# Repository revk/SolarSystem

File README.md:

# SolarSystem

Now at [Codeberg](https://codeberg.org/RevK/SolarSystem)

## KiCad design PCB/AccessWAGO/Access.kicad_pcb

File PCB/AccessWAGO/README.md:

# Access

These files are for use in [KiCad](https://www.kicad.org).

## Trademark

This is an open source project, but bear in mind you cannot sell boards bearing the Andrews & Arnold Ltd name, the A&A logo, the registered trademark AJK logo, or the GS1 allocated EANs assigned to Andrews & Arnold Ltd.

## Images

*Auto generated 2025-08-13T09:46:36*

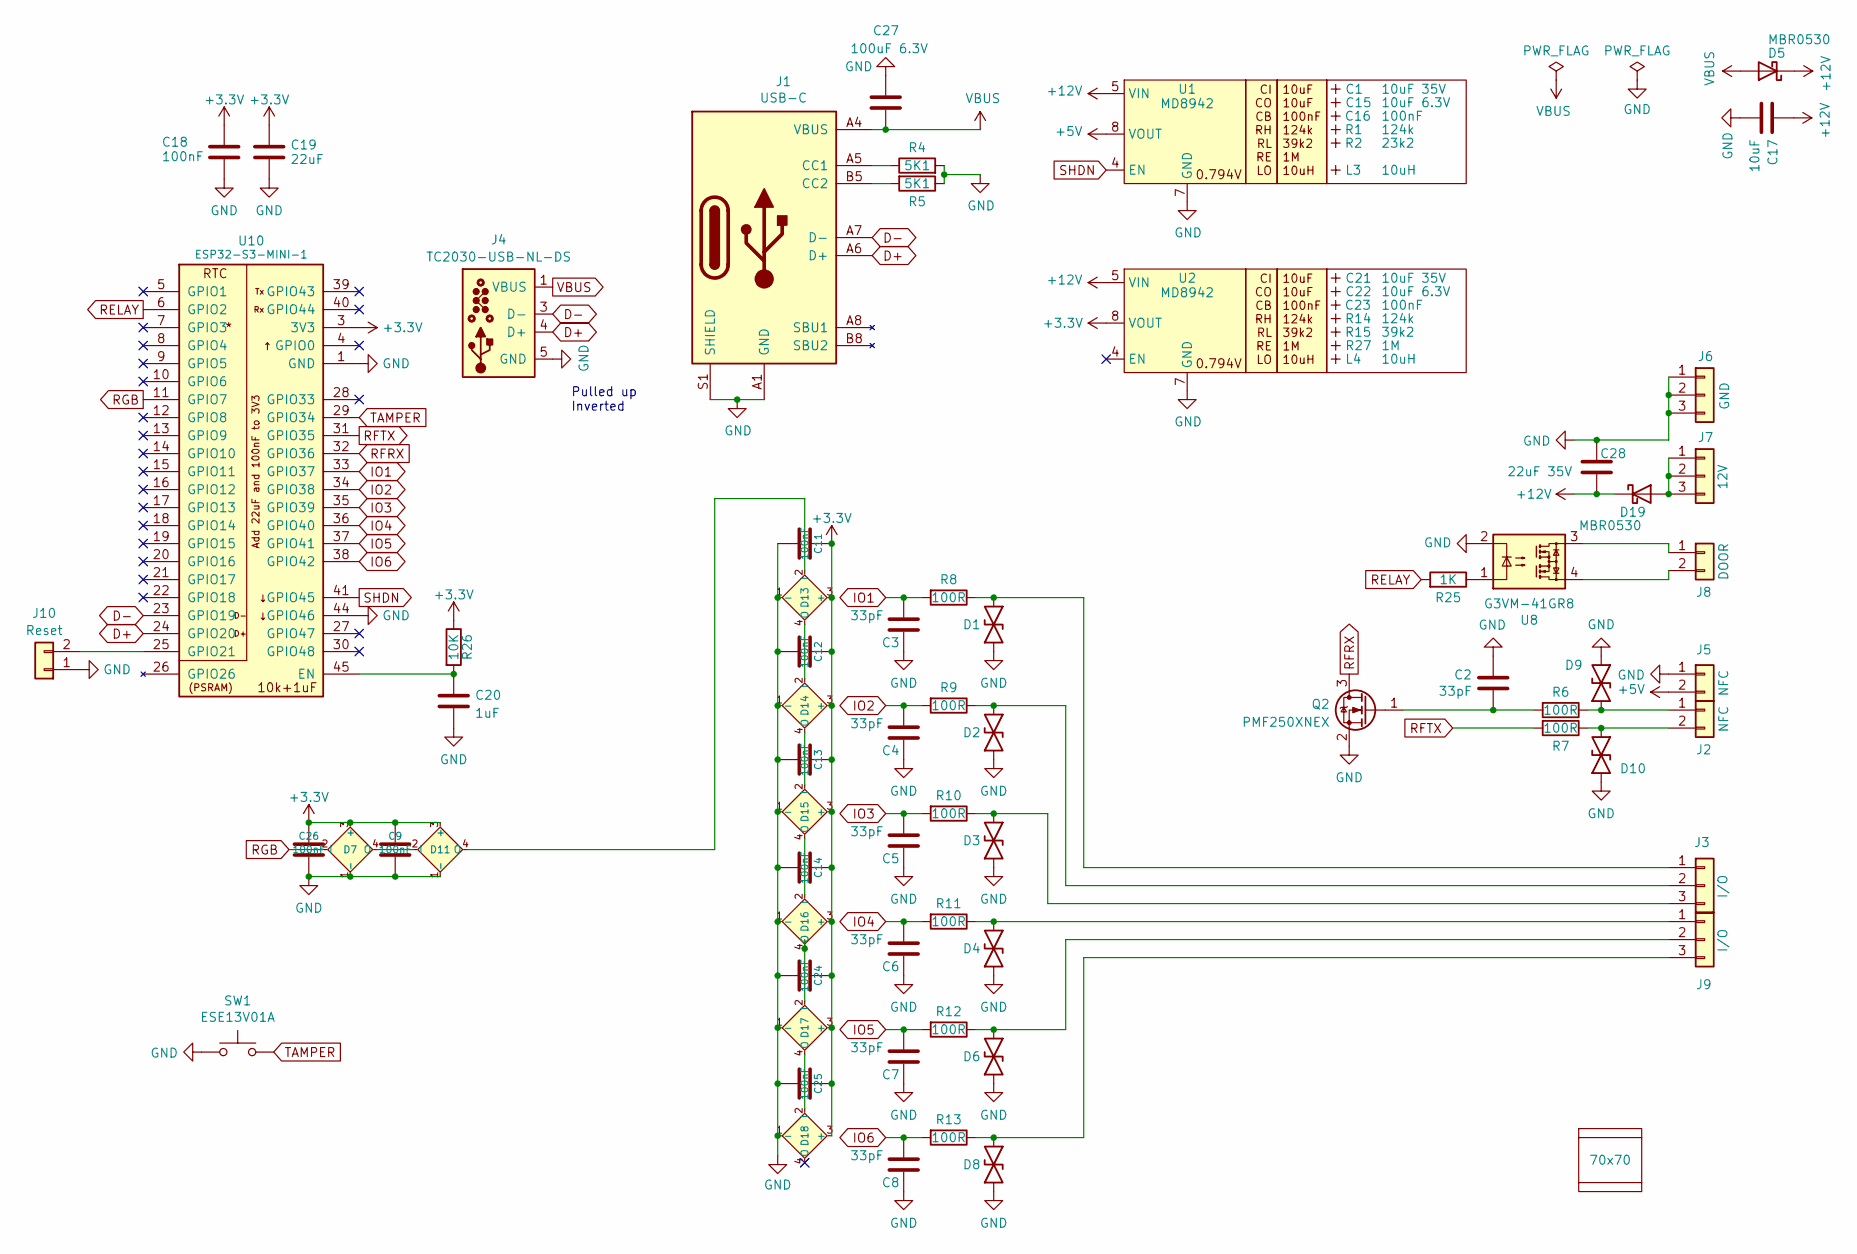
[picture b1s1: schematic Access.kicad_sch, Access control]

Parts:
C1, C21: 10uF 35V; C_0603_; MPN C194427
C2, C3, C4, C5, C6, C7, C8: 33pF; C_0201
C9, C18, C26: 100nF; C_0201
C11, C12, C13, C14, C24, C25: 100nF; C_0402
C15, C22: 10uF 6.3V; C_0603_; MPN C1691
C16, C23: 100nF; C_0603_
C17: 10uF; C_0402
C19: 22uF; C_0402
C20: 1uF; C_0201
C27: 100uF 6.3V; C_1206
C28: 22uF 35V; C_1210
D1, D2, D3, D4, D6, D8, D9, D10: DFN1006-2L; MPN C5137770
D5, D19: MBR0530; D_SOD-123; MPN C5204746
D7, D11, D13, D14, D15, D16, D17, D18: XL-1010RGBC-WS2812B; SMD1615; MPN C5349954
J1: USB-C; USB-C-Socket-H; MPN C709357
J2, J5: NFC; WAGO-2060-452-998-404-S; MPN C2765055
J3, J9: I/O; WAGO-2060-453-998-404-S; MPN C2765056
J4: TC2030-USB-NL-DS; Tag-Connect_TC2030-IDC-NL_2x03_P1.27mm_Vertical
J6: GND; WAGO-2060-453-998-404-S; MPN C2765056
J7: 12V; WAGO-2060-453-998-404-S; MPN C2765056
J8: DOOR; WAGO-2060-452-998-404-S; MPN C2765055
J10: Reset; AA-Pad
L3, L4: 10uH; L_4x4_; MPN C167879
PCB1: 70x70; PCB7070
Q2: PMF250XNEX; SOT-323_SC-70; Part No PMF250XNEX
R1, R14: 124k; R_0402_
R2: 23k2; R_0402_
R4, R5: 5K1; R_0201
R6, R7, R8, R9, R10, R11, R12, R13: 100R; R_0201
R15: 39k2; R_0402_
R25: 1K; R_0201
R26: 10K; R_0201
R27: 1M; R_0402_
SW1: ESE13V01A; ESE13
U1, U2: MD8942; SOT-23-6-MD8942; MPN C2684786
U8: G3VM-41GR8; SO-4_4.4x4.3mm_P2.54mm; MPN C2691601
U10: ESP32-S3-MINI-1; MPN C3013941
V1, V2: VCUT70

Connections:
+3.3V: C9.1, C11.1, C12.1, C13.1, C14.1, C18.1, C19.1, C24.1, C25.1, C26.1, D7.3 (+), D11.3 (+), D13.3 (+), D14.3 (+), D15.3 (+), D16.3 (+), D17.3 (+), D18.3 (+), R26.1, U2.8 (VOUT), U10.3 (3V3)
+5V: J5.2, U1.8 (VOUT)
+12V: C17.1, C28.2, D5.1 (K), D19.1 (K), U1.5 (VIN), U2.5 (VIN)
D+: J1.A6 (D+), J1.B6 (D+), J4.4 (D+), U10.24 (GPIO20)
D-: J1.A7 (D-), J1.B7 (D-), J4.2 (NC), J4.3 (D-), J4.6 (NC), U10.23 (GPIO19)
GND: C2.1, C3.1, C4.1, C5.1, C6.1, C7.1, C8.1, C9.2, C11.2, C12.2, C13.2, C14.2, C17.2, C18.2, C19.2, C20.2, C24.2, C25.2, C26.2, C27.1, C28.1, D1.1, D2.1, D3.1, D4.1, D6.1, D7.1 (-), D8.1, D9.1, D10.1, D11.1 (-), D13.1 (-), D14.1 (-), D15.1 (-), D16.1 (-), D17.1 (-), D18.1 (-), J1.A1 (GND), J1.A12 (GND), J1.B1 (GND), J1.B12 (GND), J1.S1 (SHIELD), J4.5 (GND), J5.1, J6.1, J6.2, J6.3, J10.1, Q2.2 (S), R4.2, R5.1, SW1.2, U1.2 (GND), U1.7 (GND), U2.2 (GND), U2.7 (GND), U8.2, U10.1 (GND), U10.2 (GND), U10.42 (GND), U10.43 (GND), U10.44 (GPIO46), U10.46 (GND), U10.47 (GND), U10.48 (GND), U10.49 (GND), U10.50 (GND), U10.51 (GND), U10.52 (GND), U10.53 (GND), U10.54 (GND), U10.55 (GND), U10.56 (GND), U10.57 (GND), U10.58 (GND), U10.59 (GND), U10.60 (GND), U10.61 (GND), U10.62 (GND), U10.63 (GND), U10.64 (GND), U10.65 (GND)
IO1: C3.2, R8.2, U10.33 (GPIO37)
IO2: C4.2, R9.2, U10.34 (GPIO38)
IO3: C5.2, R10.2, U10.35 (GPIO39)
IO4: C6.2, R11.2, U10.36 (GPIO40)
IO5: C7.2, R12.2, U10.37 (GPIO41)
IO6: C8.2, R13.2, U10.38 (GPIO42)
unnamed: D7.4 (O), D11.2 (I)
unnamed: D11.4 (O), D13.2 (I)
unnamed: D13.4 (O), D14.2 (I)
unnamed: D14.4 (O), D15.2 (I)
unnamed: D15.4 (O), D16.2 (I)
unnamed: D16.4 (O), D17.2 (I)
unnamed: D17.4 (O), D18.2 (I)
unnamed: D19.2 (A), J7.1, J7.2, J7.3
unnamed: J1.A5 (CC1), R4.1
unnamed: J1.B5 (CC2), R5.2
unnamed: D9.2, J2.1, R6.1
unnamed: D10.2, J2.2, R7.1
unnamed: D1.2, J3.1, R8.1
unnamed: D2.2, J3.2, R9.1
unnamed: D3.2, J3.3, R10.1
unnamed: J8.1, U8.3
unnamed: J8.2, U8.4
unnamed: D4.2, J9.1, R11.1
unnamed: D6.2, J9.2, R12.1
unnamed: D8.2, J9.3, R13.1
unnamed: J10.2, U10.25 (GPIO21)
unnamed: C2.2, Q2.1 (G), R6.2
unnamed: R25.1, U8.1
unnamed: C20.1, R26.2, U10.45 (EN)
RELAY: R25.2, U10.6 (GPIO2)
RFRX: Q2.3 (D), U10.32 (GPIO36)
RFTX: R7.2, U10.31 (GPIO35)
RGB: D7.2 (I), U10.11 (GPIO7)
SHDN: U1.4 (EN), U10.41 (GPIO45)
TAMPER: SW1.1, U10.29 (GPIO34)
VBUS: C27.2, D5.2 (A), J1.A4 (VBUS), J1.A9 (VBUS), J1.B4 (VBUS), J1.B9 (VBUS), J4.1 (VBUS)

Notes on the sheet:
Pulled up Inverted

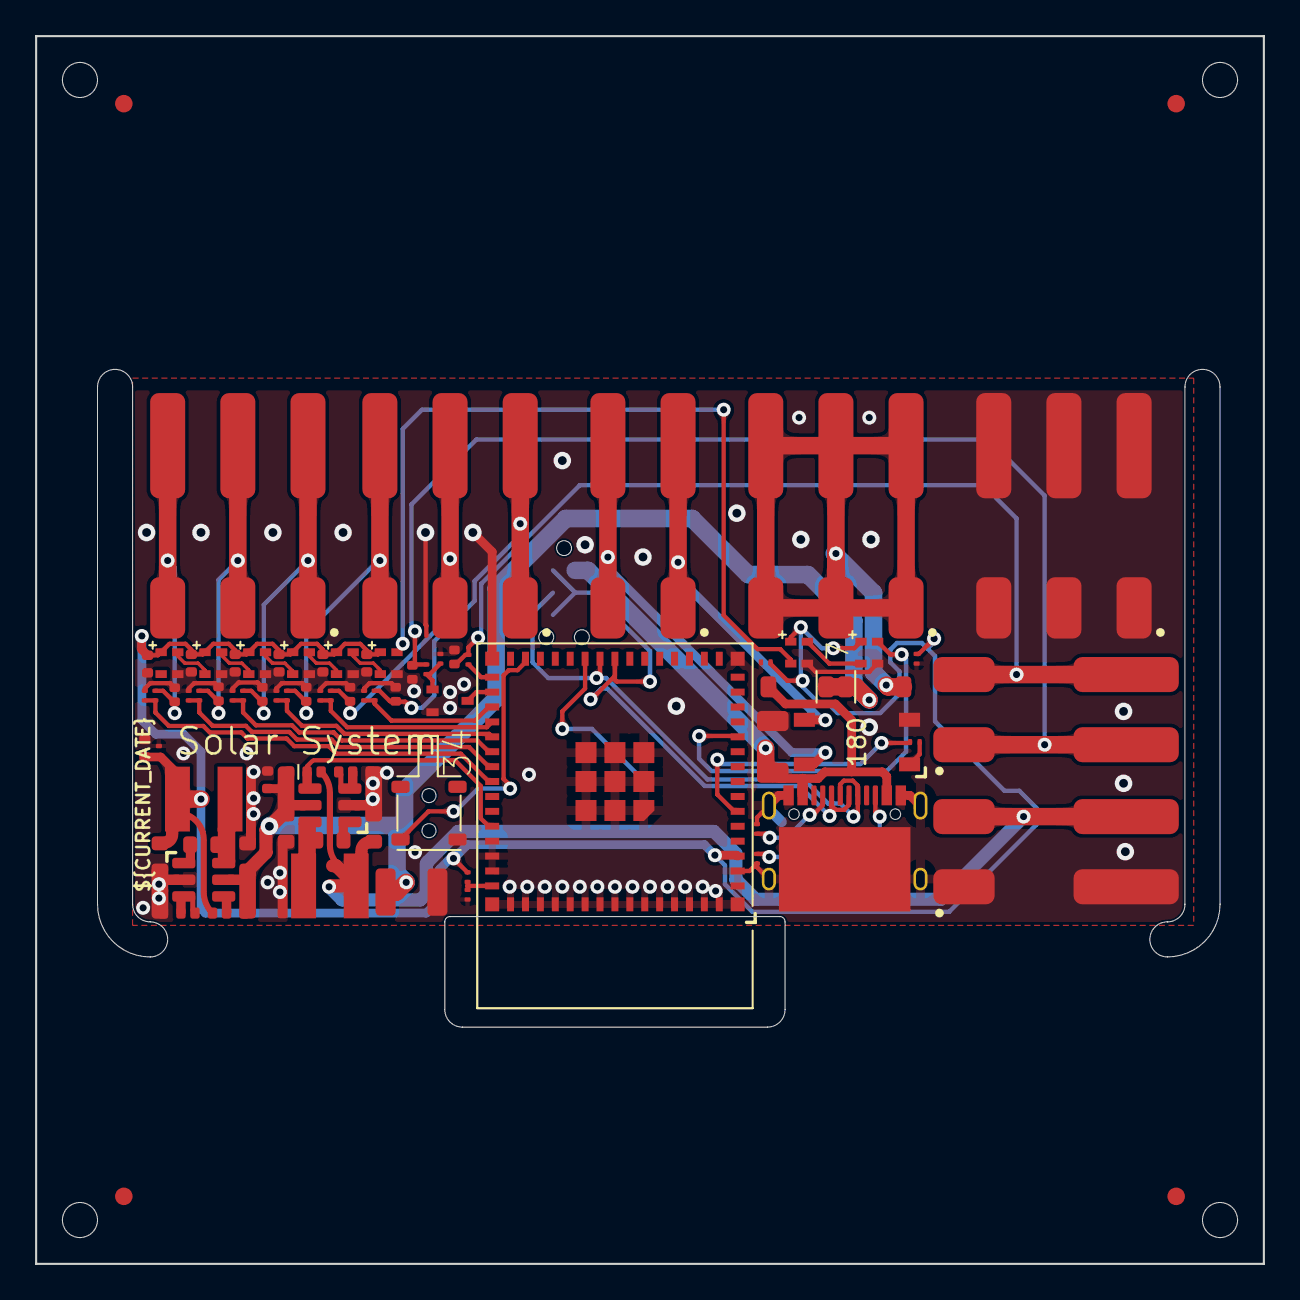
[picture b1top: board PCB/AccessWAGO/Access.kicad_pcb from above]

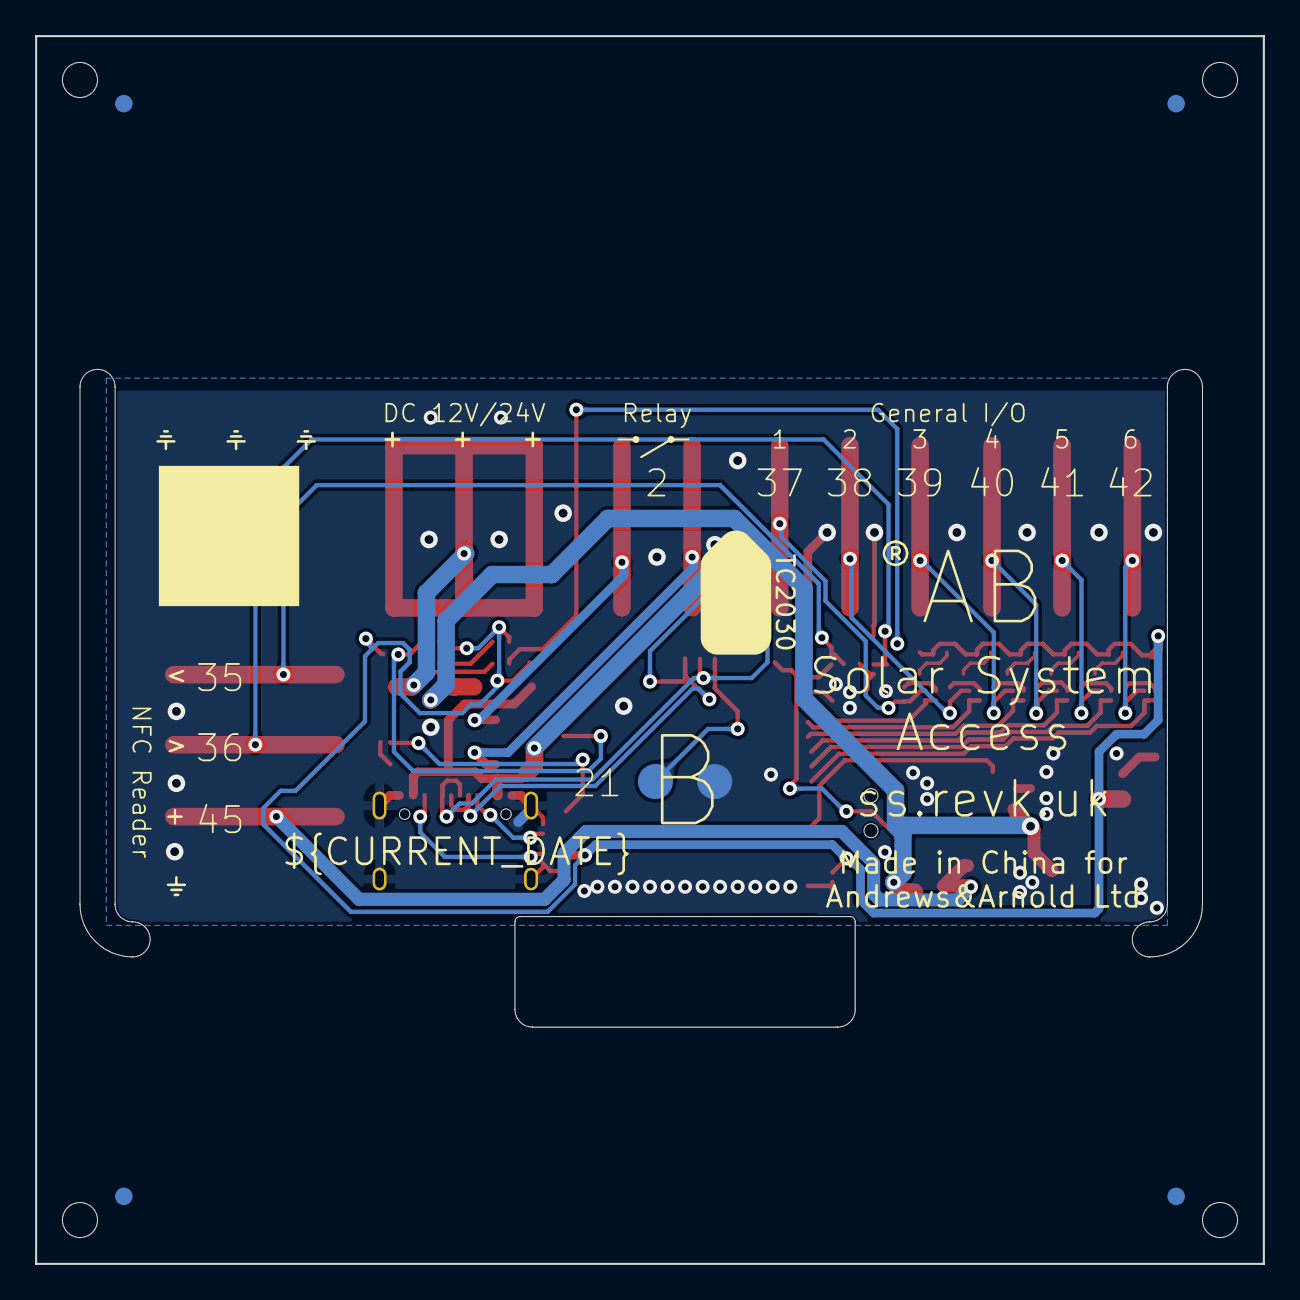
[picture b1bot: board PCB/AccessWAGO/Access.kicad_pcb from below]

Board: 2 copper layers, 70.0 x 70.0 mm, 83 parts (2 on the bottom side), 43 nets.

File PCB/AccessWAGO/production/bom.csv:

Designator,Footprint,Quantity,Value,LCSC Part #
"C1, C21",C_0603_,2,10uF 35V,C194427
"C11, C12, C13, C14, C18, C24, C25, C26, C9",C_0402,9,100nF,
"C15, C22",C_0603_,2,10uF 6.3V,C1691
"C16, C23",C_0603_,2,100nF,
C17,C_0402,1,10uF,
C19,C_0402,1,22uF,
"C2, C3, C4, C5, C6, C7, C8",C_0402,7,33pF,
C20,C_0402,1,1uF,
C27,C_1206,1,100uF 6.3V,
C28,C_1210,1,22uF 35V,
"D1, D10, D2, D3, D4, D6, D8, D9",DFN1006-2L,8,~,C5137770
"D11, D13, D14, D15, D16, D17, D18, D7",SMD1010,8,XL-1010RGBC-WS2812B,C5349953
"D19, D5",D_SOD-123,2,MBR0530,C5204746
J1,USB-C-Socket-H,1,USB-C,C709357
"J2, J5",WAGO-2060-452-998-404,2,NFC,C2765055
"J3, J9",WAGO-2060-453-998-404,2,I/O,C2765056
J6,WAGO-2060-453-998-404,1,GND,C2765056
J7,WAGO-2060-453-998-404,1,12V,C2765056
J8,WAGO-2060-452-998-404,1,DOOR,C2765055
"L3, L4",L_4x4_,2,10uH,C167879
Q2,SOT-323_SC-70,1,PMF250XNEX,C504047
"R1, R14",R_0402_,2,124k,
"R10, R11, R12, R13, R6, R7, R8, R9",R_0402,8,100R,
R15,R_0402_,1,39k2,
R2,R_0402_,1,23k2,
R25,R_0402,1,1K,
R26,R_0402,1,10K,
R27,R_0402_,1,1M,
"R4, R5",R_0402,2,5K1,
SW1,ESE13,1,ESE13V01A,
"U1, U2",SOT-23-6-MD8942,2,MD8942,C2684786
U10,ESP32-S3-MINI-1,1,ESP32-S3-MINI-1,C3013941
U8,SO-4_4.4x4.3mm_P2.54mm,1,G3VM-41GR8,C2691601

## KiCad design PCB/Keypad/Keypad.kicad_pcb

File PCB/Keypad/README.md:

# Keypad

These files are for use in [KiCad](https://www.kicad.org).

## Trademark

This is an open source project, but bear in mind you cannot sell boards bearing the Andrews & Arnold Ltd name, the A&A logo, the registered trademark AJK logo, or the GS1 allocated EANs assigned to Andrews & Arnold Ltd.

## Images

*Auto generated 2025-08-12T13:42:20*

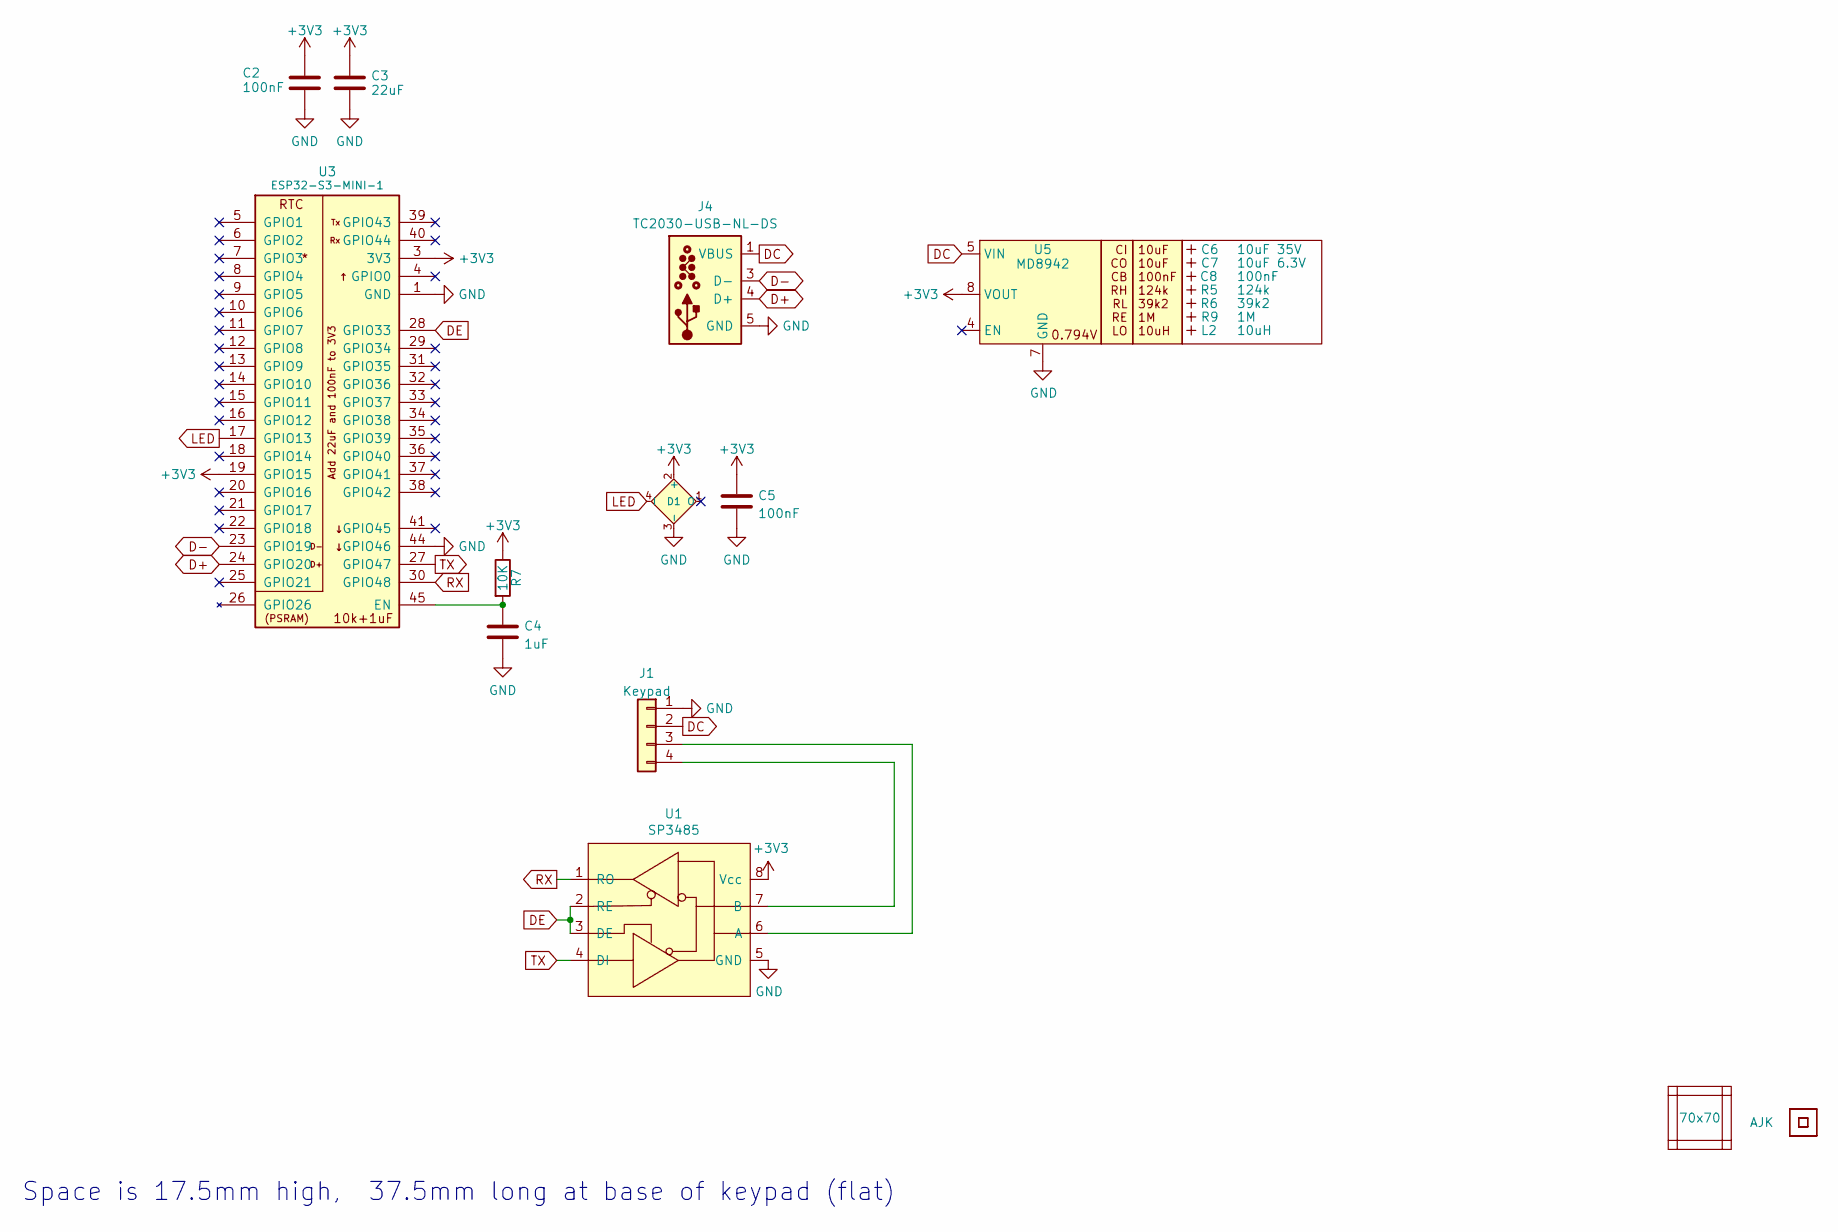
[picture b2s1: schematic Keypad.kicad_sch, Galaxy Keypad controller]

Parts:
C2, C5: 100nF; C_0402
C3: 22uF; C_0603
C4: 1uF; C_0402
C6: 10uF 35V; C_0603_; MPN C194427
C7: 10uF 6.3V; C_0603_; MPN C1691
C8: 100nF; C_0603_
D1: XL-1010RGBC-WS2812B; SMD1010; MPN C5349953
J1: Keypad; Molex_MiniSPOX_H4V
J4: TC2030-USB-NL-DS; Tag-Connect_TC2030-IDC-NL_2x03_P1.27mm_Vertical
L2: 10uH; L_4x4_
Logo1: AJK
PCB1: 70x70; PCB7070
R5: 124k; R_0402_
R6: 39k2; R_0402_
R7: 10K; R_0402
R9: 1M; R_0402_
U1: SP3485; SO-8_5.3x6.2mm_P1.27mm
U3: ESP32-S3-MINI-1; MPN C3013941
U4: QR; QR-SS
U5: MD8942; SOT-23-6-MD8942; MPN C2684786
V1, V3, V4, V6: VCUT70N

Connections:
+3V3: C2.1, C3.1, C5.1, D1.2 (+), R7.1, U1.8 (Vcc), U3.3 (3V3), U3.19 (GPIO15), U5.8 (VOUT)
D+: J4.4 (D+), U3.24 (GPIO20)
D-: J4.2 (NC), J4.3 (D-), J4.6 (NC), U3.23 (GPIO19)
DC: J1.2, J4.1 (VBUS), U5.5 (VIN)
DE: U1.2 (RE), U1.3 (DE), U3.28 (GPIO33)
GND: C2.2, C3.2, C4.2, C5.2, D1.3 (-), J1.1, J4.5 (GND), U1.5 (GND), U3.1 (GND), U3.2 (GND), U3.42 (GND), U3.43 (GND), U3.44 (GPIO46), U3.46 (GND), U3.47 (GND), U3.48 (GND), U3.49 (GND), U3.50 (GND), U3.51 (GND), U3.52 (GND), U3.53 (GND), U3.54 (GND), U3.55 (GND), U3.56 (GND), U3.57 (GND), U3.58 (GND), U3.59 (GND), U3.60 (GND), U3.61 (GND), U3.62 (GND), U3.63 (GND), U3.64 (GND), U3.65 (GND), U5.2 (GND), U5.7 (GND)
LED: D1.4 (I), U3.17 (GPIO13)
unnamed: J1.3, U1.6 (A)
unnamed: J1.4, U1.7 (B)
unnamed: C4.1, R7.2, U3.45 (EN)
RX: U1.1 (RO), U3.30 (GPIO48)
TX: U1.4 (DI), U3.27 (GPIO47)

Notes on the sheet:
Space is 17.5mm high, 37.5mm long at base of keypad (flat)

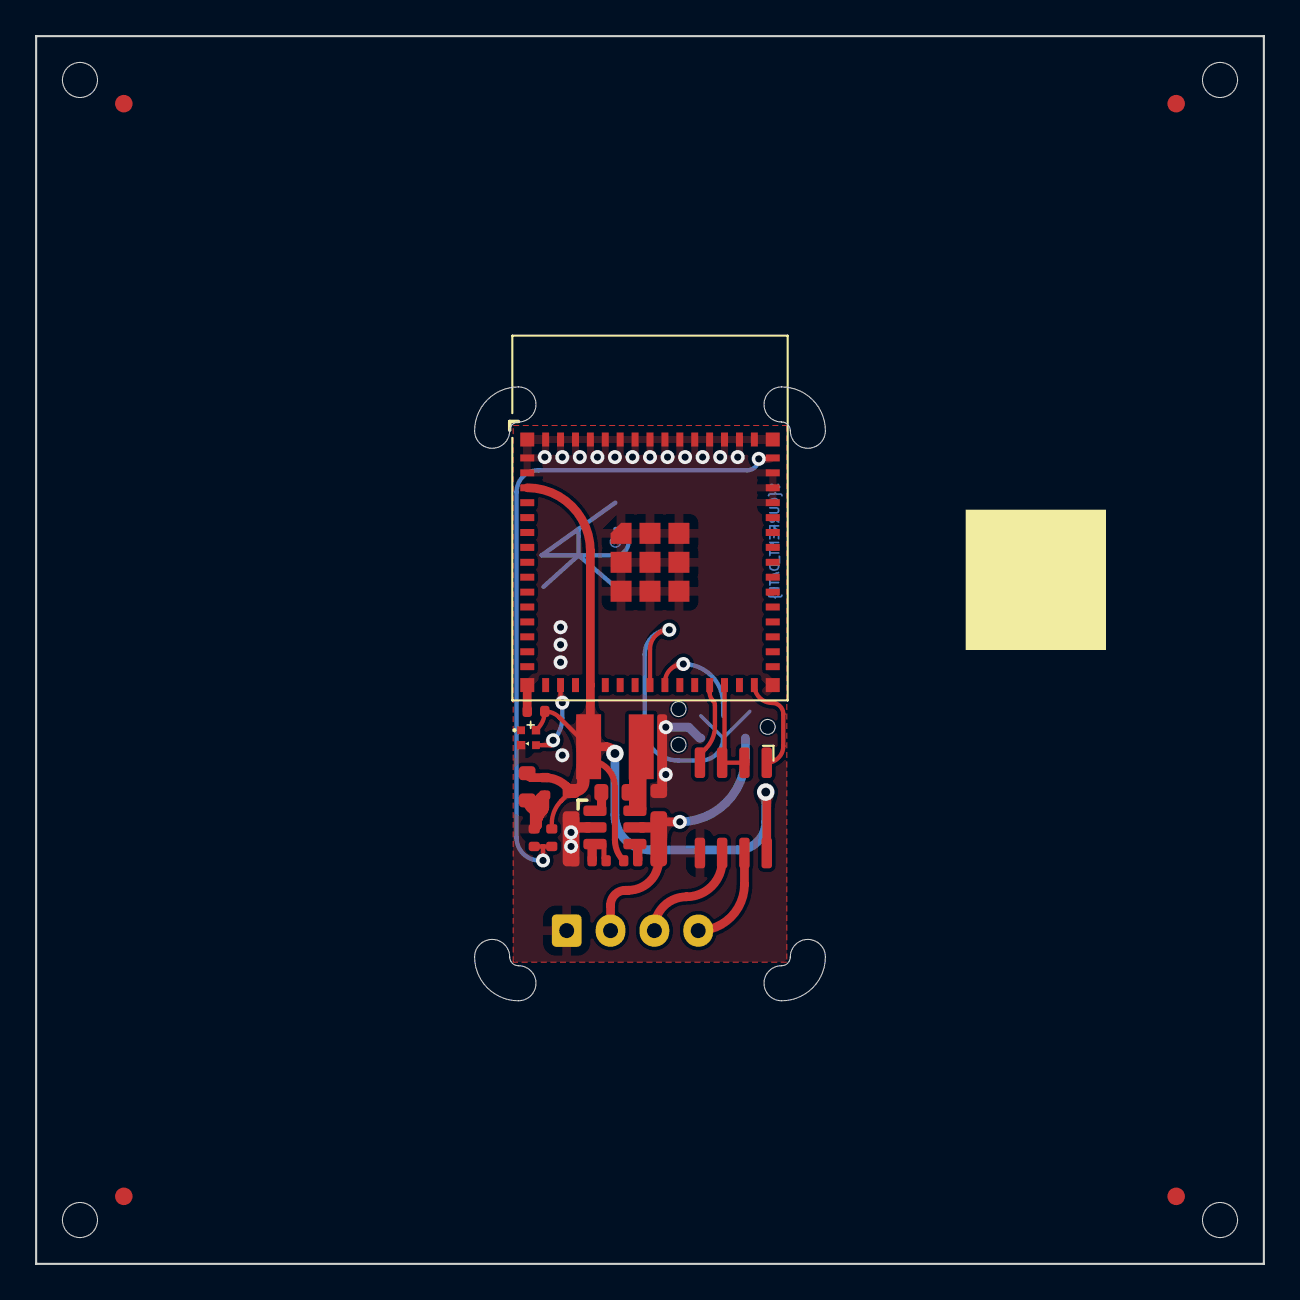
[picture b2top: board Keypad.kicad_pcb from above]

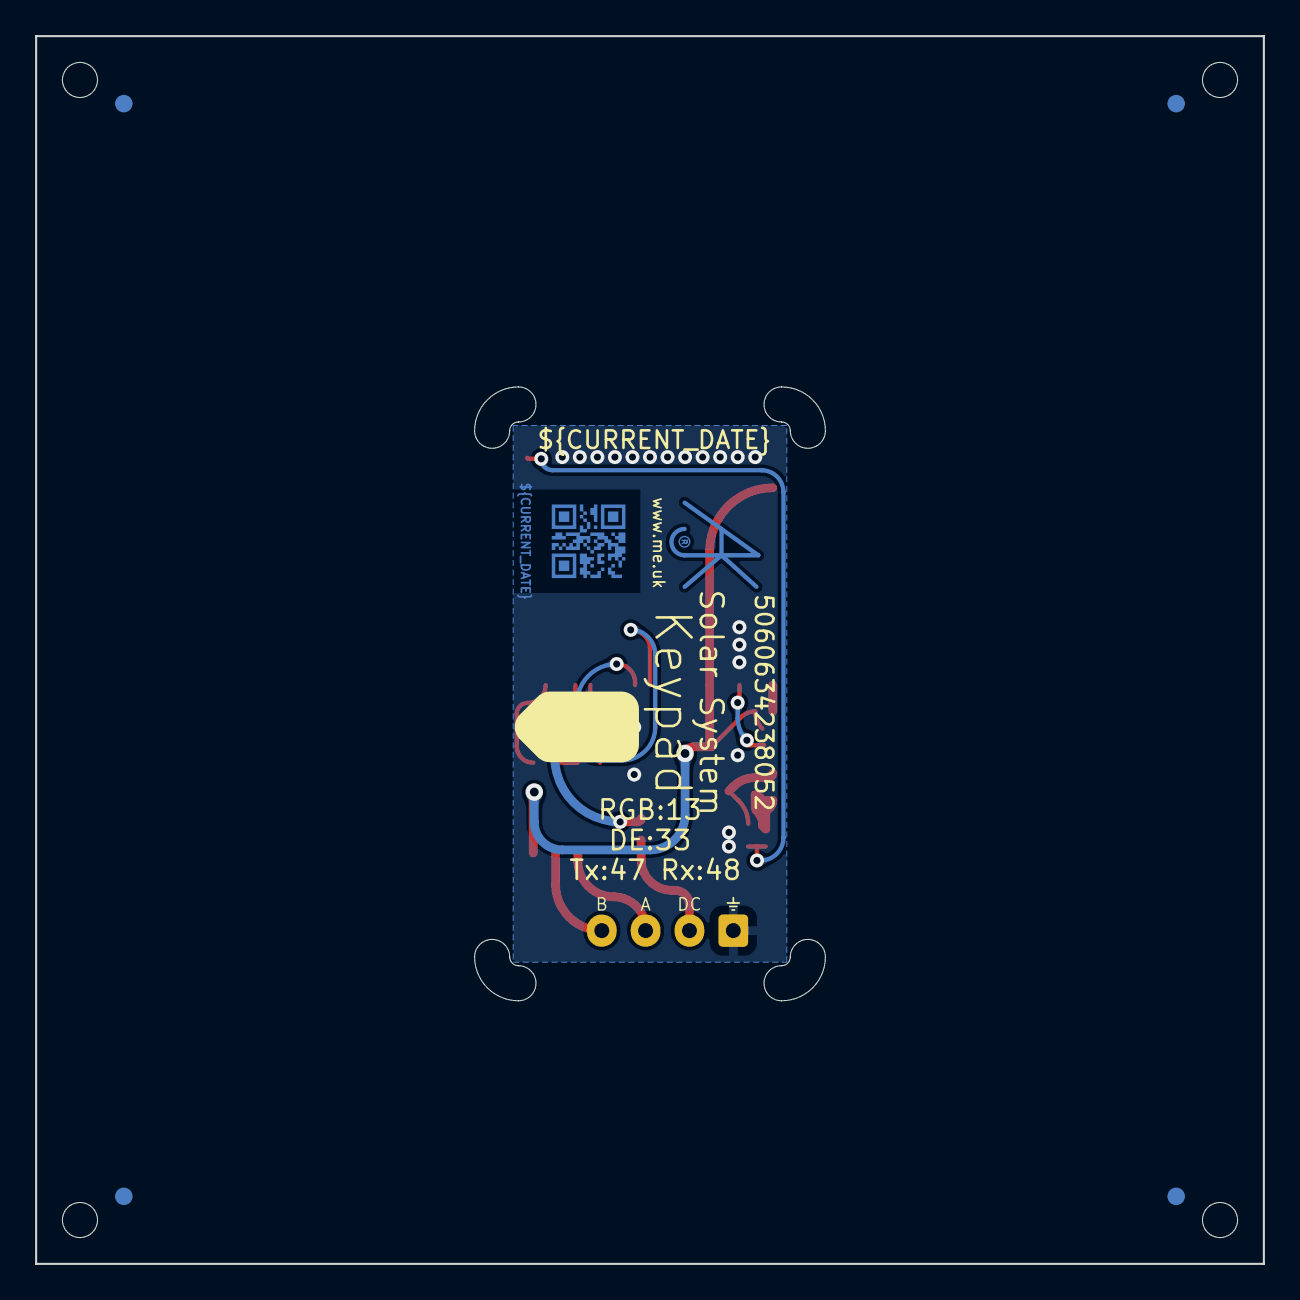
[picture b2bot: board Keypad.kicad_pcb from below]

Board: 2 copper layers, 70.0 x 70.0 mm, 25 parts (3 on the bottom side), 12 nets.

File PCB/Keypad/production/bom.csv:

Designator,Footprint,Quantity,Value,LCSC Part #
"C2, C5",C_0402,2,100nF,
C3,C_0603,1,22uF,
C4,C_0402,1,1uF,
C6,C_0603_,1,10uF 35V,C194427
C7,C_0603_,1,10uF 6.3V,C1691
C8,C_0603_,1,100nF,
D1,SMD1010,1,XL-1010RGBC-WS2812B,C5349953
J1,Molex_MiniSPOX_H4V,1,Keypad,
L2,L_4x4_,1,10uH,
R5,R_0402_,1,124k,
R6,R_0402_,1,39k2,
R7,R_0402,1,10K,
R9,R_0402_,1,1M,
U1,SO-8_3.9x4.9mm_P1.27mm,1,SP3485,
U3,ESP32-S3-MINI-1,1,ESP32-S3-MINI-1,C3013941
U5,SOT-23-6-MD8942,1,MD8942,C2684786

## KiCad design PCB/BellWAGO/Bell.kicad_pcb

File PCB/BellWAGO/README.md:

# Bell

These files are for use in [KiCad](https://www.kicad.org).

## Trademark

This is an open source project, but bear in mind you cannot sell boards bearing the Andrews & Arnold Ltd name, the A&A logo, the registered trademark AJK logo, or the GS1 allocated EANs assigned to Andrews & Arnold Ltd.

## Images

*Auto generated 2025-08-12T13:36:08*

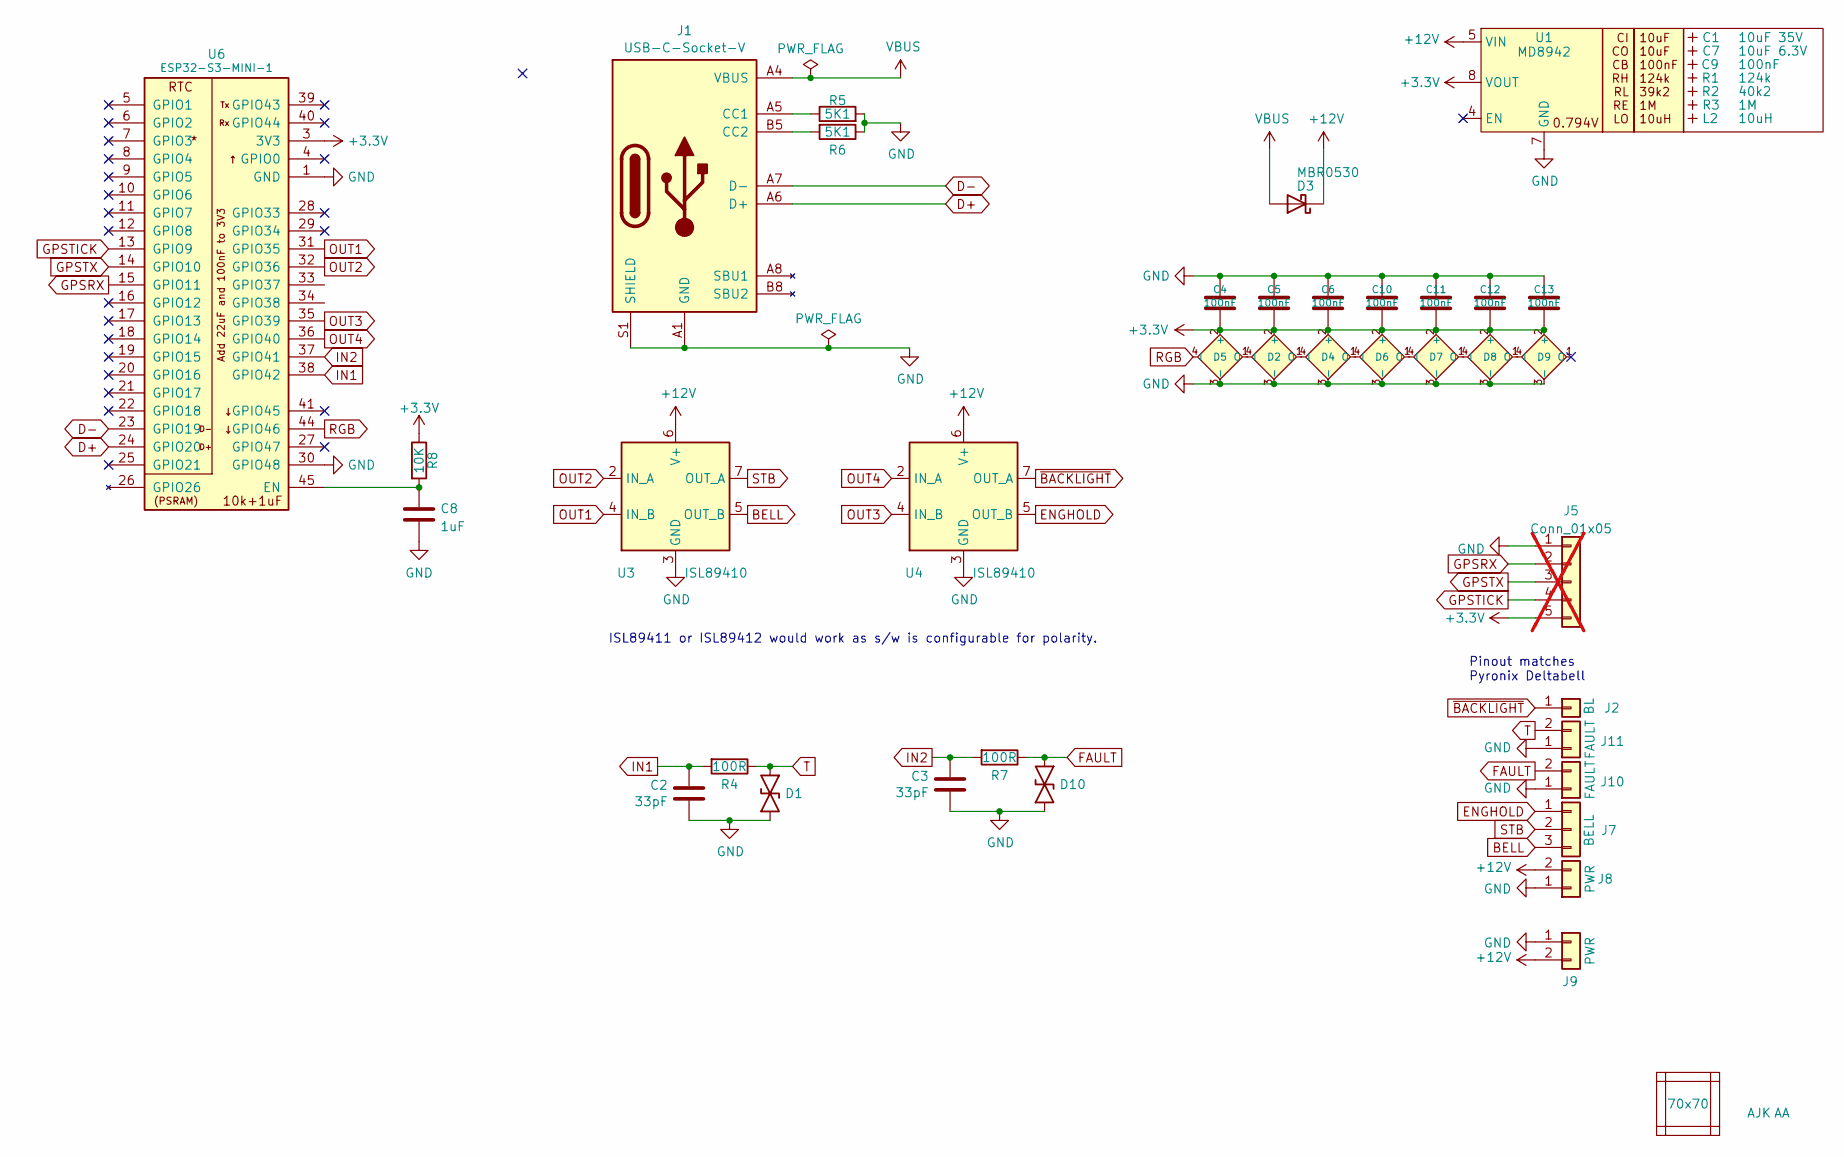
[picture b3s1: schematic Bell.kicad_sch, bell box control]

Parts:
AJK1: AJK
C1: 10uF 35V; C_0603_; MPN C194427
C2, C3: 33pF; C_0402
C4, C5, C6, C10, C11, C12, C13: 100nF; C_0402
C7: 10uF 6.3V; C_0603_; MPN C1691
C8: 1uF; C_0402
C9: 100nF; C_0603_
D1, D10: DFN1006-2L; MPN C5137770
D2, D4, D5, D6, D7, D8, D9: XL-1010RGBC-WS2812B; SMD1010; MPN C5349953
D3: MBR0530; D_SOD-123; MPN C5204746
J1: USB-C-Socket-V; USB-C-Socket-H; MPN C709357
J2: BL; WAGO-2060-451-998-404; MPN C2765054
J5: Conn_01x05; PTSM-HH-5-RA-SMD; not fitted
J7: BELL; WAGO-2060-453-998-404; MPN C2765056
J8, J9: PWR; WAGO-2060-452-998-404; MPN C2765055
J10, J11: FAULT; WAGO-2060-452-998-404; MPN C2765055
L2: 10uH; L_4x4_; MPN C167879
PCB1: 70x70; PCB7070
R1: 124k; R_0402_
R2: 40k2; R_0402_
R3: 1M; R_0402_
R4, R7: 100R; R_0402
R5, R6: 5K1; R_0402
R8: 10K; R_0402
U1: MD8942; SOT-23-6-MD8942; MPN C2684786
U3, U4: ISL89410; SO-8_3.9x4.9mm_P1.27mm; MPN C635887
U6: ESP32-S3-MINI-1; MPN C3013941
U7: AA
V1, V2, V3, V4: VCUT70N

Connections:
+3.3V: C4.2, C5.2, C6.2, C10.2, C11.2, C12.2, C13.2, D2.2 (+), D4.2 (+), D5.2 (+), D6.2 (+), D7.2 (+), D8.2 (+), D9.2 (+), J5.5, R8.1, U1.8 (VOUT), U6.3 (3V3)
+12V: D3.1 (K), J8.2, J9.2, U1.5 (VIN), U3.6 (V+), U4.6 (V+)
BELL: J7.3, U3.5 (OUT_B)
D+: J1.A6 (D+), J1.B6 (D+), U6.24 (GPIO20)
D-: J1.A7 (D-), J1.B7 (D-), U6.23 (GPIO19)
ENGHOLD: J7.1, U4.5 (OUT_B)
FAULT: D10.1, J10.2, R7.1
GND: C2.2, C3.2, C4.1, C5.1, C6.1, C8.2, C10.1, C11.1, C12.1, C13.1, D1.2, D2.3 (-), D4.3 (-), D5.3 (-), D6.3 (-), D7.3 (-), D8.3 (-), D9.3 (-), D10.2, J1.A1 (GND), J1.A12 (GND), J1.B1 (GND), J1.B12 (GND), J1.S1 (SHIELD), J5.1, J8.1, J9.1, J10.1, J11.1, R5.2, R6.1, U1.2 (GND), U1.7 (GND), U3.3 (GND), U4.3 (GND), U6.1 (GND), U6.2 (GND), U6.30 (GPIO48), U6.42 (GND), U6.43 (GND), U6.46 (GND), U6.47 (GND), U6.48 (GND), U6.49 (GND), U6.50 (GND), U6.51 (GND), U6.52 (GND), U6.53 (GND), U6.54 (GND), U6.55 (GND), U6.56 (GND), U6.57 (GND), U6.58 (GND), U6.59 (GND), U6.60 (GND), U6.61 (GND), U6.62 (GND), U6.63 (GND), U6.64 (GND), U6.65 (GND)
GPSRX: J5.2, U6.15 (GPIO11)
GPSTICK: J5.4, U6.13 (GPIO9)
GPSTX: J5.3, U6.14 (GPIO10)
IN1: C2.1, R4.2, U6.38 (GPIO42)
IN2: C3.1, R7.2, U6.37 (GPIO41)
unnamed: D2.4 (I), D5.1 (O)
unnamed: D2.1 (O), D4.4 (I)
unnamed: D4.1 (O), D6.4 (I)
unnamed: D6.1 (O), D7.4 (I)
unnamed: D7.1 (O), D8.4 (I)
unnamed: D8.1 (O), D9.4 (I)
unnamed: J1.A5 (CC1), R5.1
unnamed: J1.B5 (CC2), R6.2
unnamed: C8.1, R8.2, U6.45 (EN)
OUT1: U3.4 (IN_B), U6.31 (GPIO35)
OUT2: U3.2 (IN_A), U6.32 (GPIO36)
OUT3: U4.4 (IN_B), U6.35 (GPIO39)
OUT4: U4.2 (IN_A), U6.36 (GPIO40)
RGB: D5.4 (I), U6.44 (GPIO46)
STB: J7.2, U3.7 (OUT_A)
T: D1.1, J11.2, R4.1
VBUS: D3.2 (A), J1.A4 (VBUS), J1.A9 (VBUS), J1.B4 (VBUS), J1.B9 (VBUS)
~BACKLIGHT: J2.1, U4.7 (OUT_A)

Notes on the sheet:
Pinout matches Pyronix Deltabell
ISL89411 or ISL89412 would work as s/w is configurable for polarity.

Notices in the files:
alarmpanel.c:
Copyright (C) 2017  RevK and Andrews & Arnold Ltd
This program is free software: you can redistribute it and/or modify
it under the terms of the GNU General Public License as published by
the Free Software Foundation, either version 3 of the License, or
(at your option) any later version.
